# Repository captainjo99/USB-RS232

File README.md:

# USB-RS232

Small USB to RS232 communication module designed in [KiCad](https://www.kicad.org/).

## Front view

## Back view

## Notes

This module is based on FT232RL/FT231XS and MAX202.

Schematic is available in pdf format in the repository. Module features 3V3 to 5V level shifter. RX and TX on the pin header arer 5V TTL.

**ONLY USE FT232RL OR FT231XS, NOT BOTH AT THE SAME TIME. MODULE IS DESIGNED SO THEY CAN BE USED INTERCHANGEABLY!!!**

## Licence
Creative Commons Zero 1.0 Universal

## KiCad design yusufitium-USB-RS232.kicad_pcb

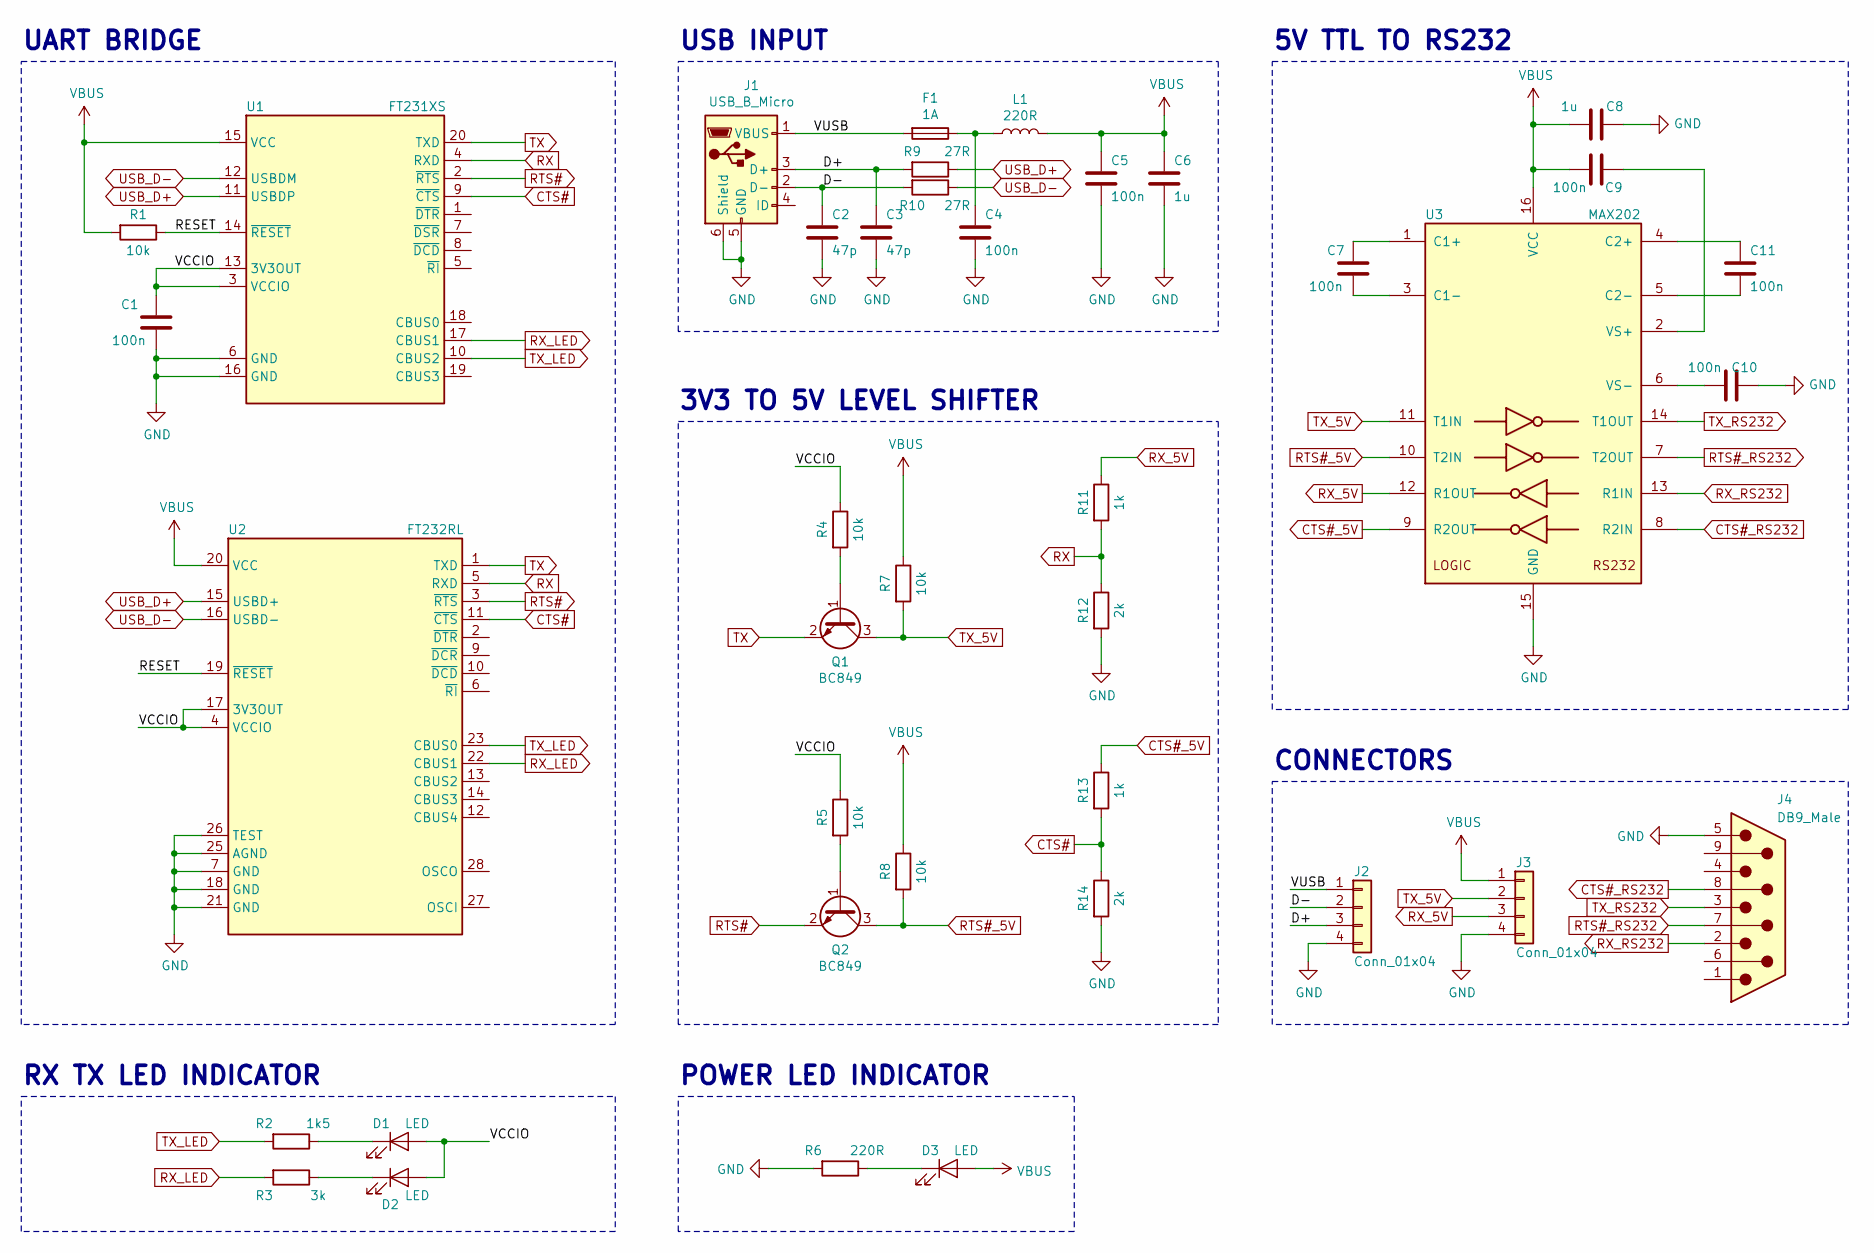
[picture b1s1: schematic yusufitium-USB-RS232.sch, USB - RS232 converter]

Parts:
C1, C4, C5, C7, C9, C10, C11: 100n; C_0603_1608Metric_Pad1.05x0.95mm_HandSolder
C2, C3: 47p; C_0603_1608Metric_Pad1.05x0.95mm_HandSolder
C6, C8: 1u; C_0603_1608Metric_Pad1.05x0.95mm_HandSolder
D1, D2, D3: LED; LED_D3.0mm
F1: 1A; Fuse_1206_3216Metric_Pad1.42x1.75mm_HandSolder
J1: USB_B_Micro; USB_Micro-B_Molex_47346-0001
J2: Conn_01x04; WireHeader_1x4
J3: Conn_01x04; PinHeader_1x04_P2.54mm_Vertical
J4: DB9_Male; DSUB-9_Male_EdgeMount_P2.77mm
L1: 220R; L_0603_1608Metric
Q1, Q2: BC849; SOT-23
R1, R4, R5, R7, R8: 10k; R_0603_1608Metric_Pad1.05x0.95mm_HandSolder
R2: 1k5; R_0603_1608Metric_Pad1.05x0.95mm_HandSolder
R3: 3k; R_0603_1608Metric_Pad1.05x0.95mm_HandSolder
R6: 220R; R_0603_1608Metric_Pad1.05x0.95mm_HandSolder
R9, R10: 27R; R_0603_1608Metric_Pad1.05x0.95mm_HandSolder
R11, R13: 1k; R_0603_1608Metric_Pad1.05x0.95mm_HandSolder
R12, R14: 2k; R_0603_1608Metric_Pad1.05x0.95mm_HandSolder
U1: FT231XS; SSOP-20_3.9x8.7mm_P0.635mm
U2: FT232RL; SSOP-28_5.3x10.2mm_P0.65mm
U3: MAX202; SOIC-16_3.9x9.9mm_P1.27mm

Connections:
/D+: C3.1, J1.3 (D+), J2.3, R9.2
/D-: C2.1, J1.2 (D-), J2.2, R10.2
/RESET: R1.1, U1.14 (~RESET), U2.19 (~RESET~)
/VCCIO: C1.1, D1.2 (A), D2.2 (A), R4.1, R5.1, U1.3 (VCCIO), U1.13 (3V3OUT), U2.4 (VCCIO), U2.17 (3V3OUT)
/VUSB: F1.2, J1.1 (VBUS), J2.1
CTS#: R13.2, R14.1, U1.9 (~CTS), U2.11 (~CTS)
CTS#_5V: R13.1, U3.9 (R2OUT)
CTS#_RS232: J4.8, U3.8 (R2IN)
GND: C1.2, C2.2, C3.2, C4.2, C5.2, C6.2, C8.1, C10.2, J1.5 (GND), J1.6 (Shield), J2.4, J3.4, J4.5, R6.2, R12.2, R14.2, U1.6 (GND), U1.16 (GND), U2.7 (GND), U2.18 (GND), U2.21 (GND), U2.25 (AGND), U2.26 (TEST), U3.15 (GND)
unnamed: C4.1, F1.1, L1.1
unnamed: C7.1, U3.1 (C1+)
unnamed: C7.2, U3.3 (C1-)
unnamed: C9.2, U3.2 (VS+)
unnamed: C10.1, U3.6 (VS-)
unnamed: C11.1, U3.4 (C2+)
unnamed: C11.2, U3.5 (C2-)
unnamed: D1.1 (K), R2.1
unnamed: D2.1 (K), R3.1
unnamed: D3.1 (K), R6.1
unnamed: Q1.1 (B), R4.2
unnamed: Q2.1 (B), R5.2
RTS#: Q2.2 (E), U1.2 (~RTS), U2.3 (~RTS)
RTS#_5V: Q2.3 (C), R8.2, U3.10 (T2IN)
RTS#_RS232: J4.7, U3.7 (T2OUT)
RX: R11.2, R12.1, U1.4 (RXD), U2.5 (RXD)
RX_5V: J3.3, R11.1, U3.12 (R1OUT)
RX_LED: R3.2, U1.17 (CBUS1), U2.22 (CBUS1)
RX_RS232: J4.2, U3.13 (R1IN)
TX: Q1.2 (E), U1.20 (TXD), U2.1 (TXD)
TX_5V: J3.2, Q1.3 (C), R7.2, U3.11 (T1IN)
TX_LED: R2.2, U1.10 (CBUS2), U2.23 (CBUS0)
TX_RS232: J4.3, U3.14 (T1OUT)
USB_D+: R9.1, U1.11 (USBDP), U2.15 (USBD+)
USB_D-: R10.1, U1.12 (USBDM), U2.16 (USBD-)
VBUS: C5.1, C6.1, C8.2, C9.1, D3.2 (A), J3.1, L1.2, R1.2, R7.1, R8.1, U1.15 (VCC), U2.20 (VCC), U3.16 (VCC)

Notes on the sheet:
UART BRIDGE
USB INPUT
3V3 TO 5V LEVEL SHIFTER
5V TTL TO RS232
CONNECTORS
RX TX LED INDICATOR
POWER LED INDICATOR

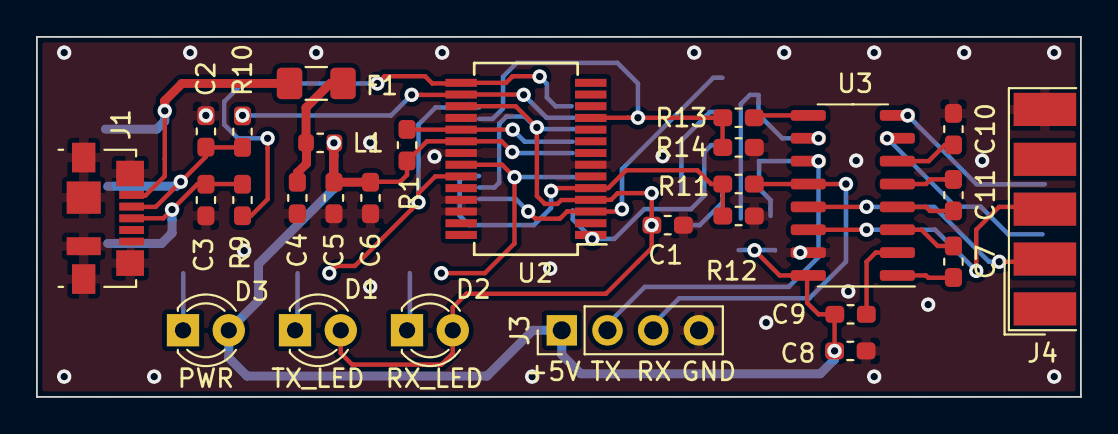
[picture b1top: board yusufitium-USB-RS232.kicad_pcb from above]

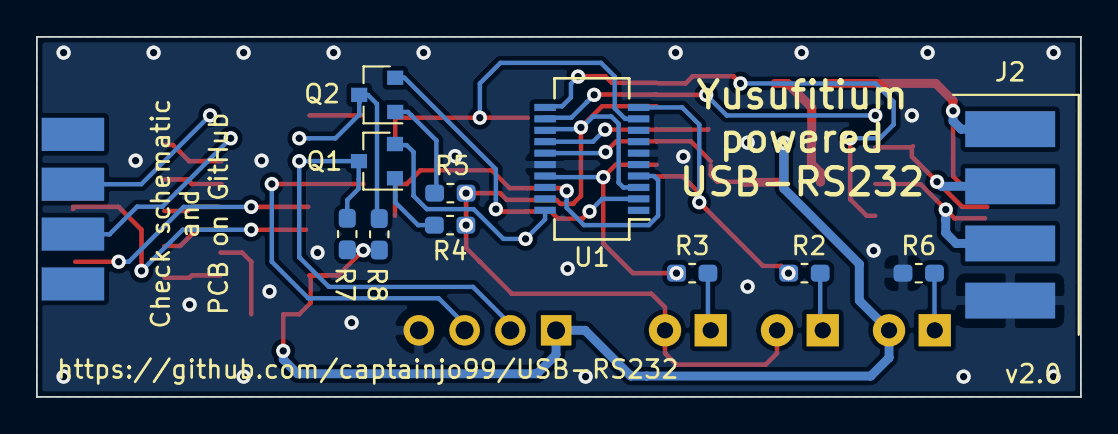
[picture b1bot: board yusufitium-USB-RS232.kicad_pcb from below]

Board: 2 copper layers, 58.0 x 20.0 mm, 39 parts (11 on the bottom side), 35 nets.

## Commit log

2022-03-06 First upload
